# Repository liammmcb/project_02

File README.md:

# Replica Lightsaber PCB

This repository contains all needed files to create a PCB for the lightsaber as outlined in the lightsaber directory. The purpose of the PCB is to recreate all hardware connectivity currently being used by the PocketBeagle.

The EAGLE folder contains all files related to the EAGLE app, a PCB designer. It contains the library file (.lbr), the schematic file (.sch) and the board layout file (.brd) for the lightsaber PCB. The MFG-folder contains all files for PCB manufacturing, including assembly files, drill files, and gerber files.

The docs folder contains a PowerPoint outlining the background of the project, along with various block diagrams. Additionally, the top and bottom layers of the PCB, along with the schematic are included in this folder.

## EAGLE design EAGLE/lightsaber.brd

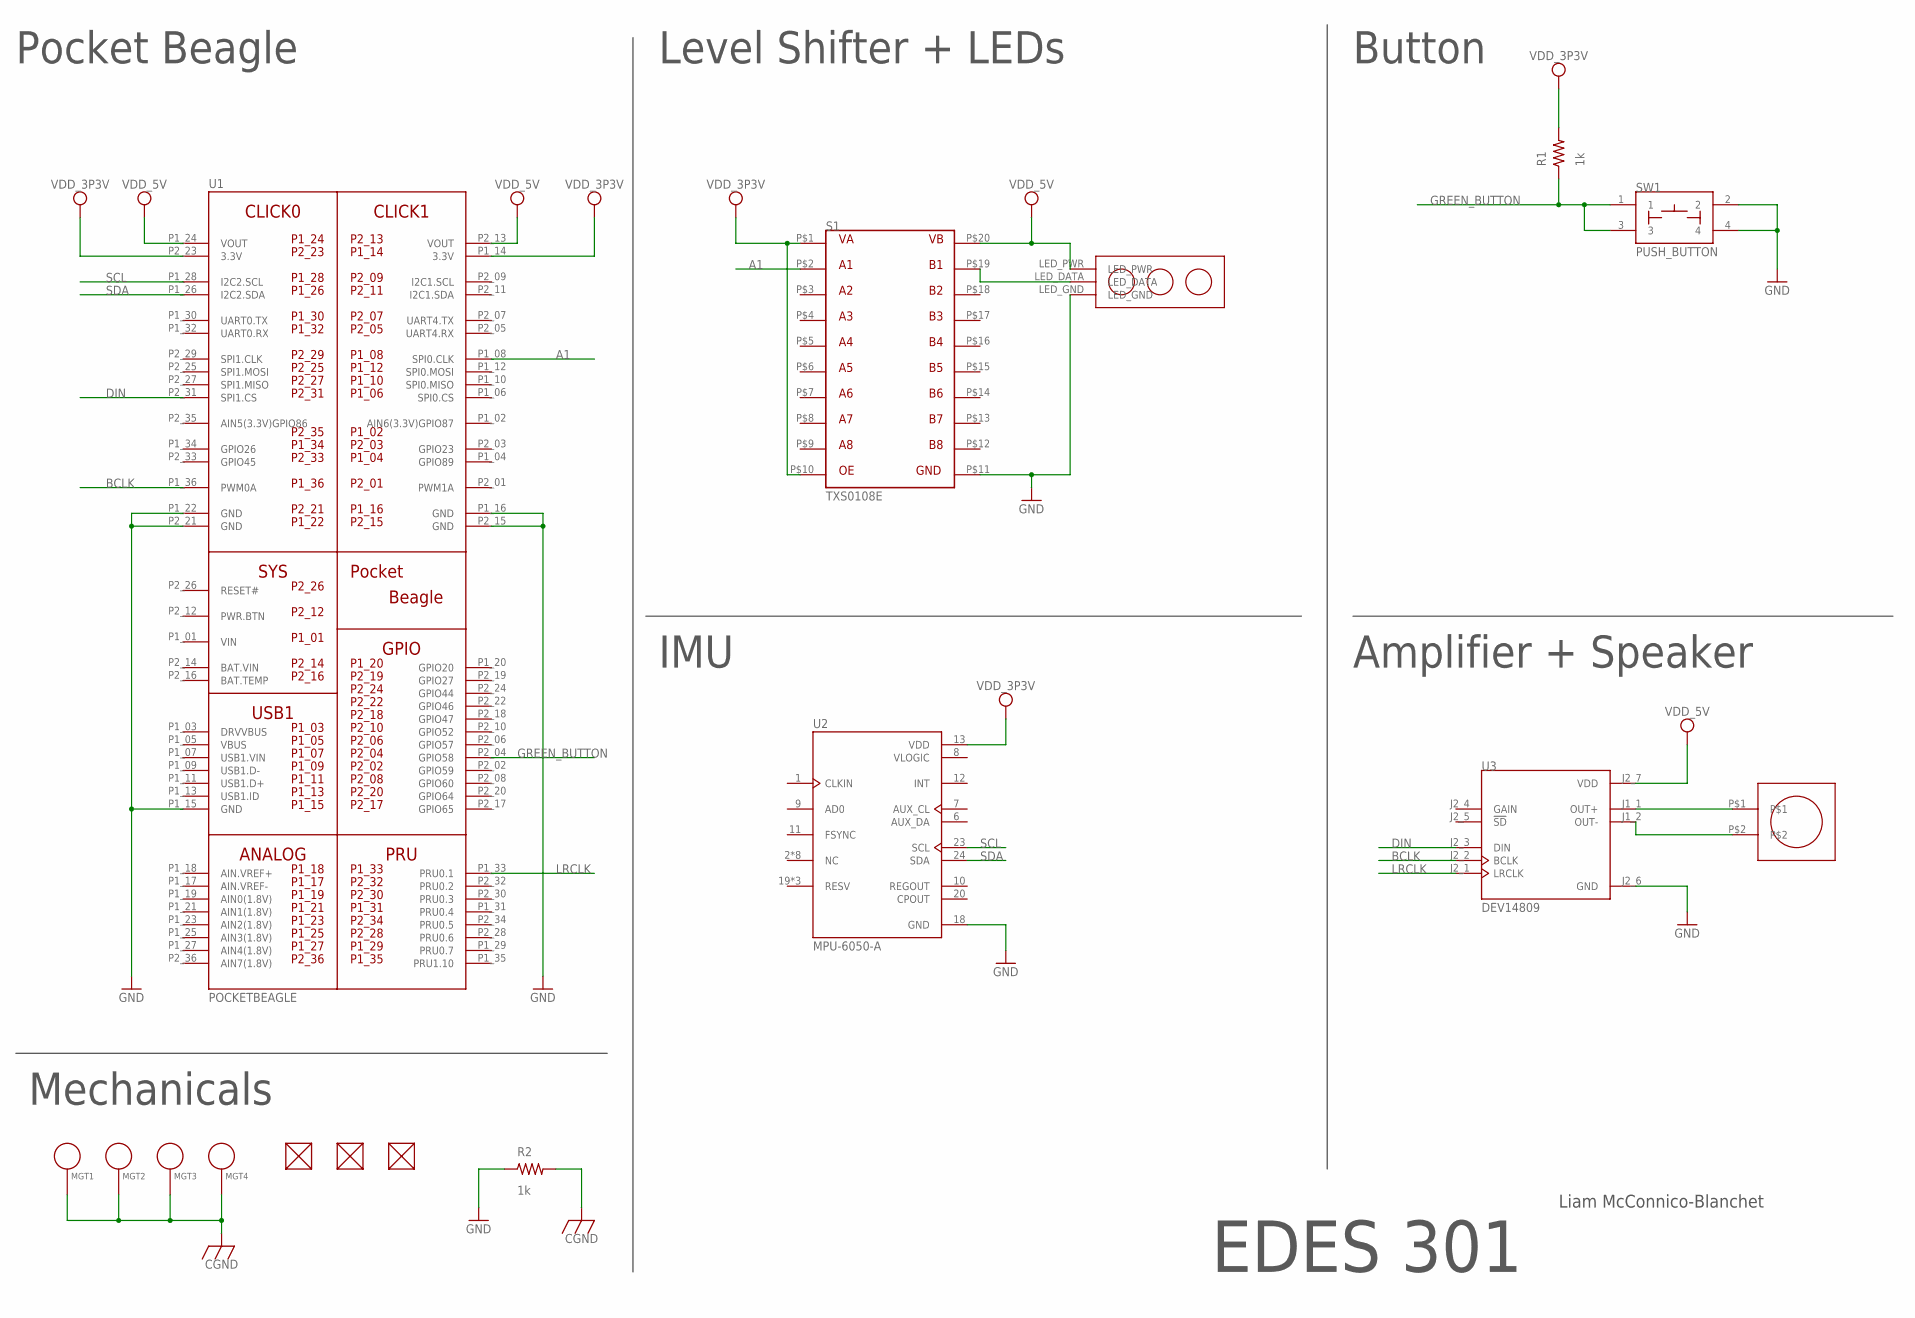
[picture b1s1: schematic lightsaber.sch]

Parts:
FUD1, FUD2, FUD3: FIDUCIAL; FIDUCIAL_40MIL
MGT1, MGT2, MGT3, MGT4: MOUNTING_HOLE
R1, R2: 1k; R0603
S1: TXS0108E
SW1: PUSH_BUTTON; BUTTON_12.5MM
U1: POCKETBEAGLE
U2: MPU-6050-A; QFN50P400X400X95-24N
U3: DEV14809; MODULE_DEV14809
U$1: LED_STRIP
U$2: SPEAKER

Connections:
A1: S1.P$2, U1.P1_08 (SPI0.CLK)
BAT.VIN: U1.P2_14 (BAT.VIN)
BCLK: U1.P1_36 (PWM0A), U3.J2_2 (BCLK)
CGND: MGT1.P$1, MGT2.P$1, MGT3.P$1, MGT4.P$1, R2.2
DIN: U1.P2_31 (SPI1.CS), U3.J2_3 (DIN)
GND: R2.1, S1.P$11, SW1.2, SW1.4, U1.P1_15 (GND), U1.P1_16 (GND), U1.P1_22 (GND), U1.P2_15 (GND), U1.P2_21 (GND), U2.18 (GND), U3.J2_6 (GND), U$1.LED_GND
GREEN_BUTTON: R1.1, SW1.1, SW1.3, U1.P2_04 (GPIO58)
LRCLK: U1.P1_33 (PRU0.1), U3.J2_1 (LRCLK)
unnamed: U3.J1_1 (OUT+), U$2.P$1
unnamed: U3.J1_2 (OUT-), U$2.P$2
unnamed: S1.P$19, U$1.LED_DATA
SCL: U1.P1_28 (I2C2.SCL), U2.23 (SCL)
SDA: U1.P1_26 (I2C2.SDA), U2.24 (SDA)
VDD_3P3V: R1.2, S1.P$1, S1.P$10, U1.P1_14 (3.3V), U1.P2_23 (3.3V), U2.13 (VDD)
VDD_5V: S1.P$20, U1.P1_24 (VOUT), U1.P2_13 (VOUT), U3.J2_7 (VDD), U$1.LED_PWR
VIN: U1.P1_01 (VIN)
VLOGIC: U2.8 (VLOGIC)

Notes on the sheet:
Pocket Beagle
Level Shifter + LEDs
Button
IMU
Amplifier + Speaker
Mechanicals
EDES 301
Liam McConnico-Blanchet

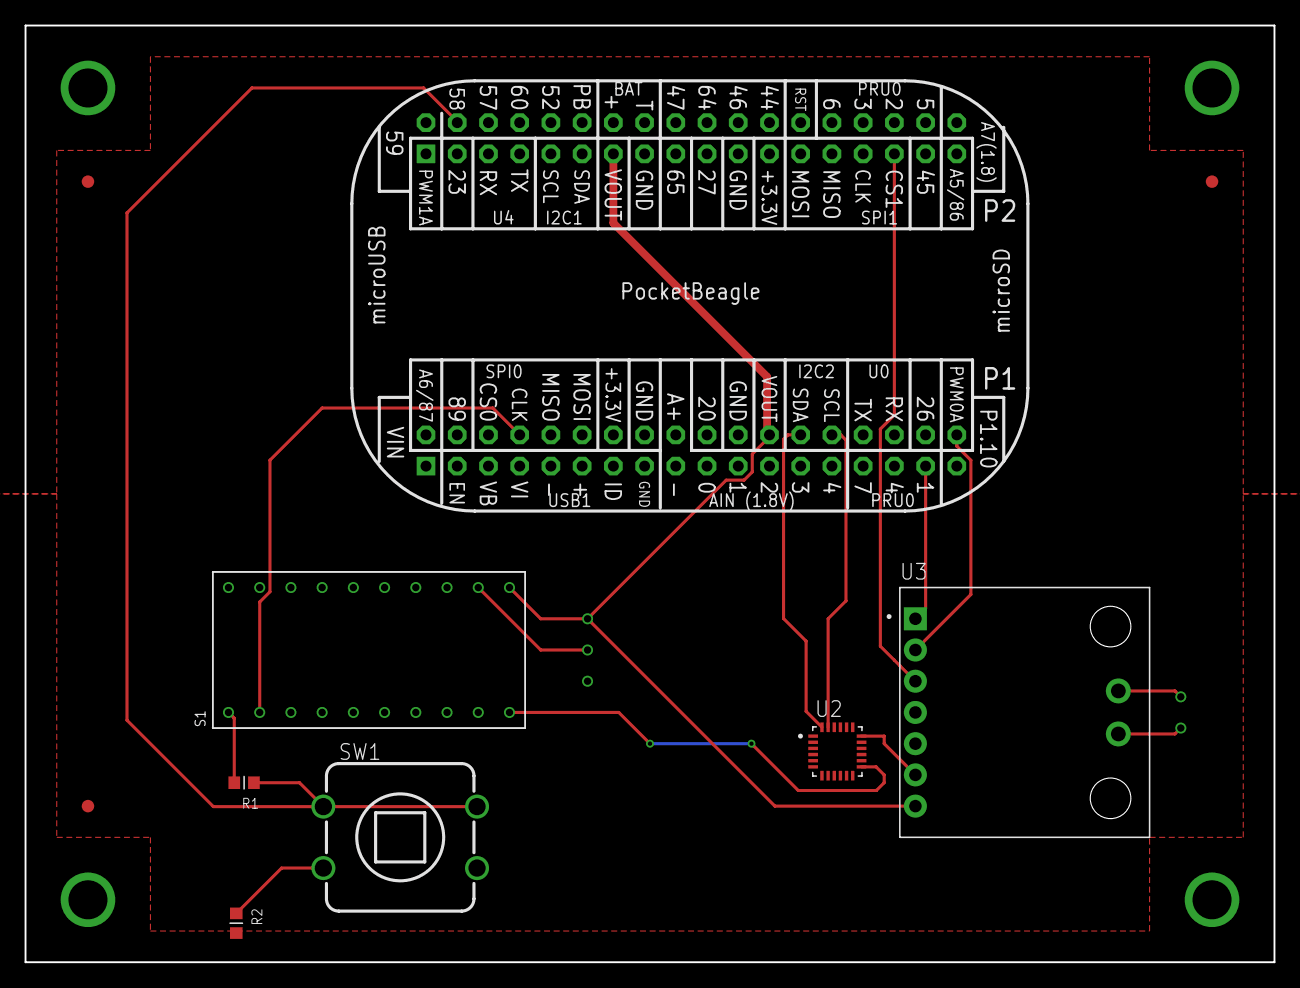
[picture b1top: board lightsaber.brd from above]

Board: 4 copper layers, 101.6 x 76.2 mm, 16 parts (0 on the bottom side), 14 nets.

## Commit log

2025-01-06 Create temp.txt
    EAGLE folder created
2025-01-06 Create temp.txt
    Created docs sub-folder
2025-01-06 Delete EAGLE/ENGI301_project_02.pptx
    Added to wrong folder
2025-01-06 Create temp.txt
    Create mfg folder
2025-01-07 Create temp.txt
    Create DrillFiles folder
2025-01-07 Create temp.txt
    Create GerberFiles folder
